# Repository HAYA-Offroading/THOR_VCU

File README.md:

# README for THOR VCU 

## Code related notes 

## PCB Design notes 

### VERSION V1.01 

V1.01 of the PCB was fabricated at Lion Circuits, and used for ESVC 2025.\
Has many errors, and the audio amplifier is not available. Power rails are incorrect, and another buck converter had to be botched into place, and a 5v rail had to be added. <br/>

Images: <br/>

[Front Side of fabricated PCB](https://github.com/HAYA-Offroading/THOR_VCU/blob/main/PCB_V1-01/FrontSide.jpeg)<br/>

[Back Side of fabricated PCB](https://github.com/HAYA-Offroading/THOR_VCU/blob/main/PCB_V1-01/BackSide.jpeg)<br/>

**DO NOT REFABRICATE WITHOUT FIXES.**

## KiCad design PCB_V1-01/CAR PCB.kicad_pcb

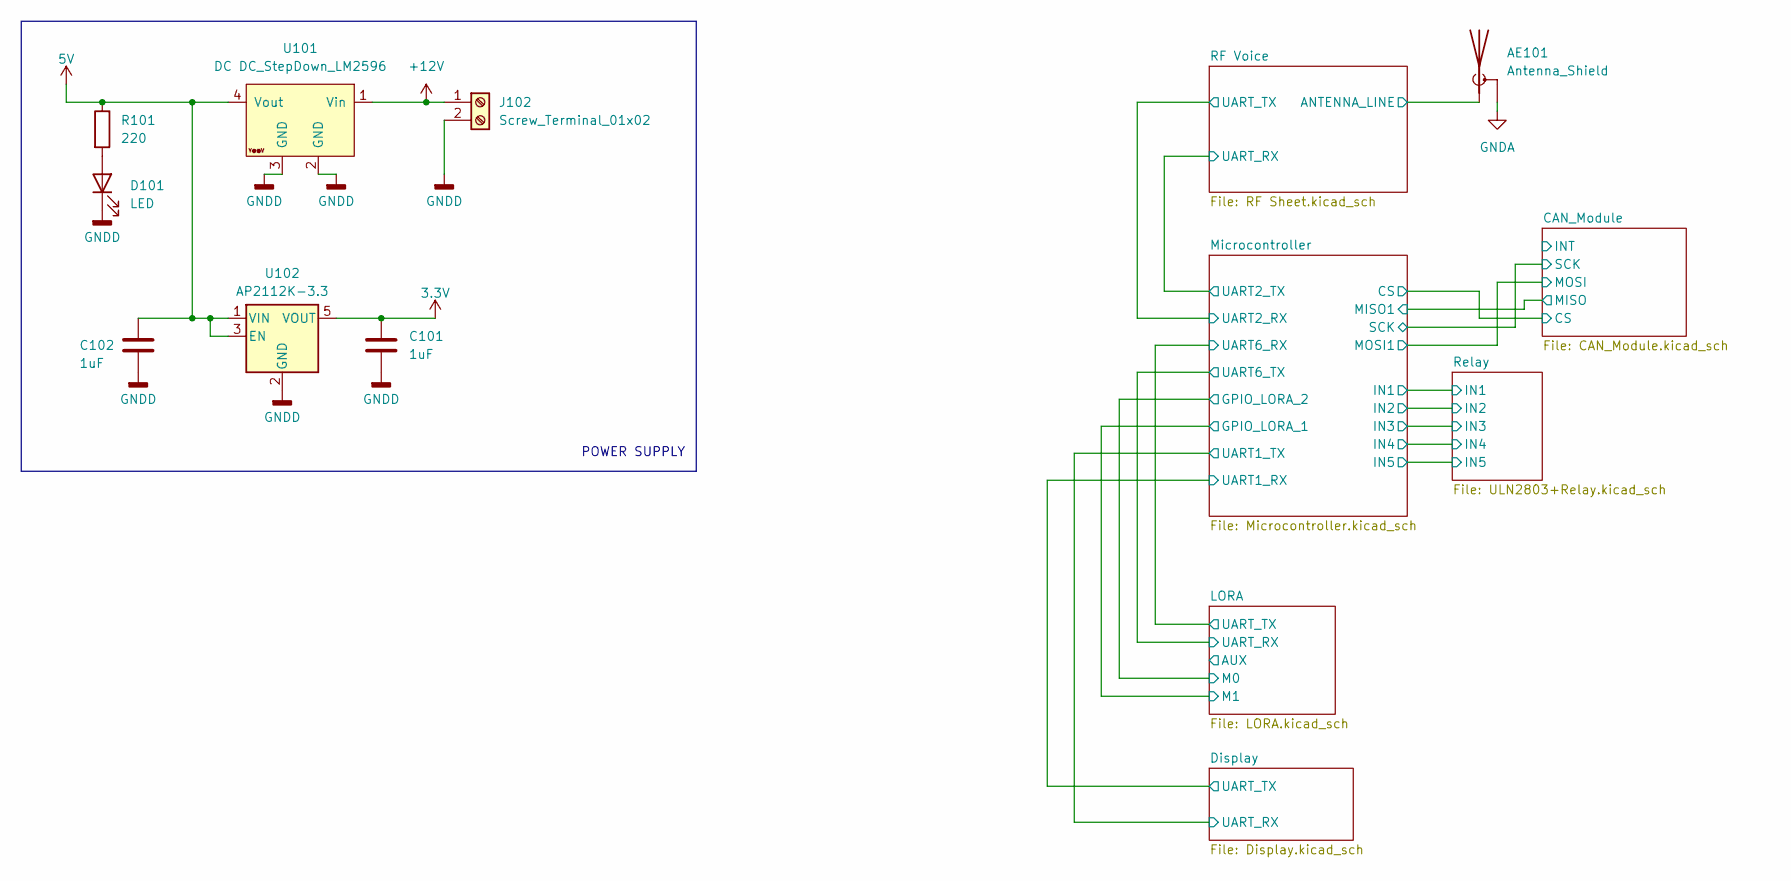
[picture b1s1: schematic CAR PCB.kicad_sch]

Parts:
AE101: Antenna_Shield; SMA_Amphenol_132134-11_Vertical
C101, C102: 1uF; C_0603_1608Metric_Pad1.08x0.95mm_HandSolder
D101: LED; LED_1206_3216Metric_Pad1.42x1.75mm_HandSolder
J102: Screw_Terminal_01x02; TerminalBlock_Phoenix_MKDS-3-2-5.08_1x02_P5.08mm_Horizontal
R101: 220; R_0805_2012Metric_Pad1.20x1.40mm_HandSolder
U101: DC DC_StepDown_LM2596; DCDC_StepDown_LM2596
U102: AP2112K-3.3; SOT-23-5

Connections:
3.3V: C101.1, U102.5 (VOUT); also elsewhere on the board
5V: C102.1, R101.1, U101.4 (Vout), U102.1 (VIN), U102.3 (EN); also elsewhere on the board
+12V: J102.1, U101.1 (Vin); also elsewhere on the board
/RF Voice/ANTENNA_LINE: AE101.1 (A); also elsewhere on the board
GNDA: AE101.2 (Shield); also elsewhere on the board
GNDD: C101.2, C102.2, D101.1 (K), J102.2, U101.2 (GND), U101.3 (GND), U102.2 (GND); also elsewhere on the board
unnamed: D101.2 (A), R101.2

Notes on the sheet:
POWER SUPPLY

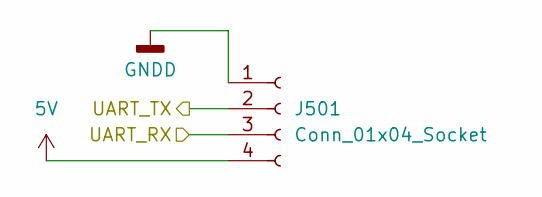
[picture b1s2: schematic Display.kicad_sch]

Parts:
J501: Conn_01x04_Socket; JST_XH_B4B-XH-A_1x04_P2.50mm_Vertical

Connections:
5V: J501.4; also elsewhere on the board
/Display/UART_RX: J501.3; also elsewhere on the board
/Display/UART_TX: J501.2; also elsewhere on the board
GNDD: J501.1; also elsewhere on the board

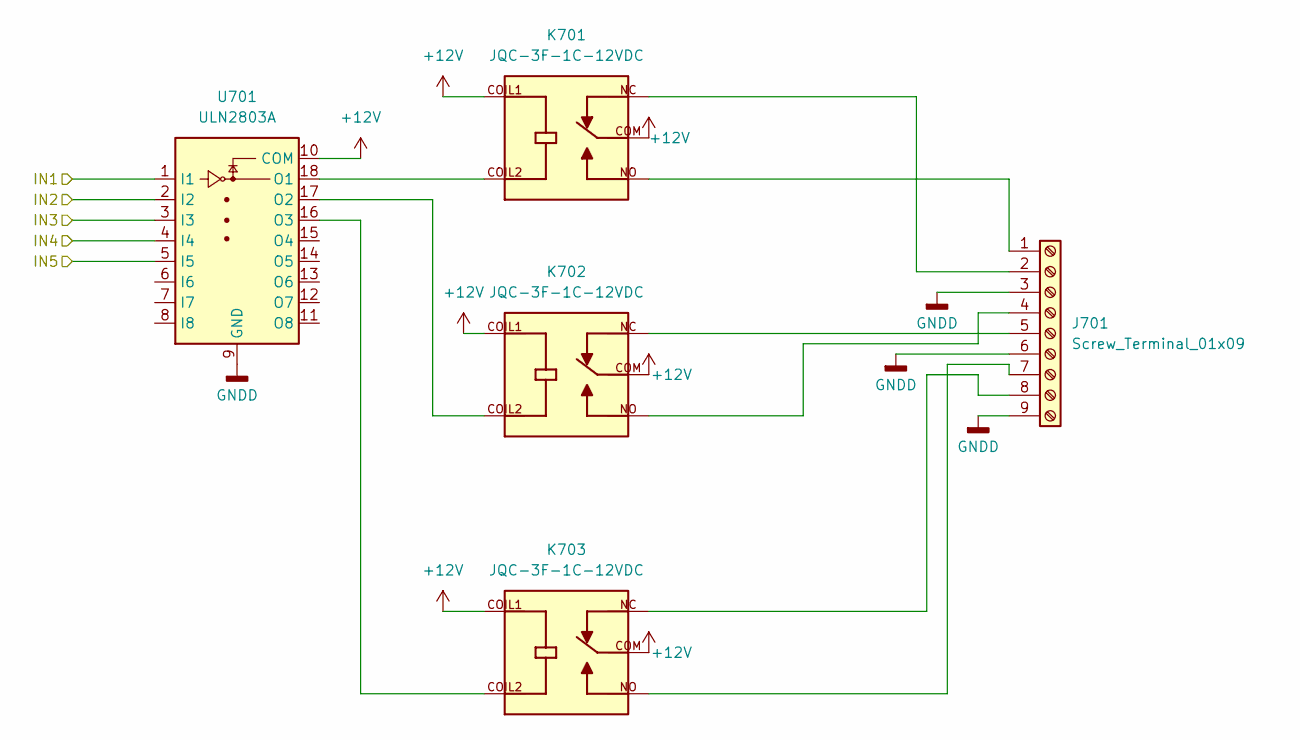
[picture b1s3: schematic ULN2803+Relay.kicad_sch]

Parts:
J701: Screw_Terminal_01x09; TerminalBlock_Phoenix_MKDS-1,5-9_1x09_P5.00mm_Horizontal
K701, K702, K703: JQC-3F-1C-12VDC; RELAY_JQC-3F-1C-24VDC; PARTREV N/A
U701: ULN2803A; SOIC-18W_7.5x11.6mm_P1.27mm

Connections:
+12V: K701.COIL1, K701.COM, K702.COIL1, K702.COM, K703.COIL1, K703.COM, U701.10 (COM); also elsewhere on the board
/Microcontroller/IN1: U701.1 (I1); also elsewhere on the board
/Microcontroller/IN2: U701.2 (I2); also elsewhere on the board
/Microcontroller/IN3: U701.3 (I3); also elsewhere on the board
/Microcontroller/IN4: U701.4 (I4); also elsewhere on the board
/Microcontroller/IN5: U701.5 (I5); also elsewhere on the board
GNDD: J701.3, J701.6, J701.9, U701.9 (GND); also elsewhere on the board
unnamed: J701.1, K701.NO
unnamed: J701.2, K701.NC
unnamed: J701.4, K702.NO
unnamed: J701.5, K702.NC
unnamed: J701.7, K703.NO
unnamed: J701.8, K703.NC
unnamed: K701.COIL2, U701.18 (O1)
unnamed: K702.COIL2, U701.17 (O2)
unnamed: K703.COIL2, U701.16 (O3)

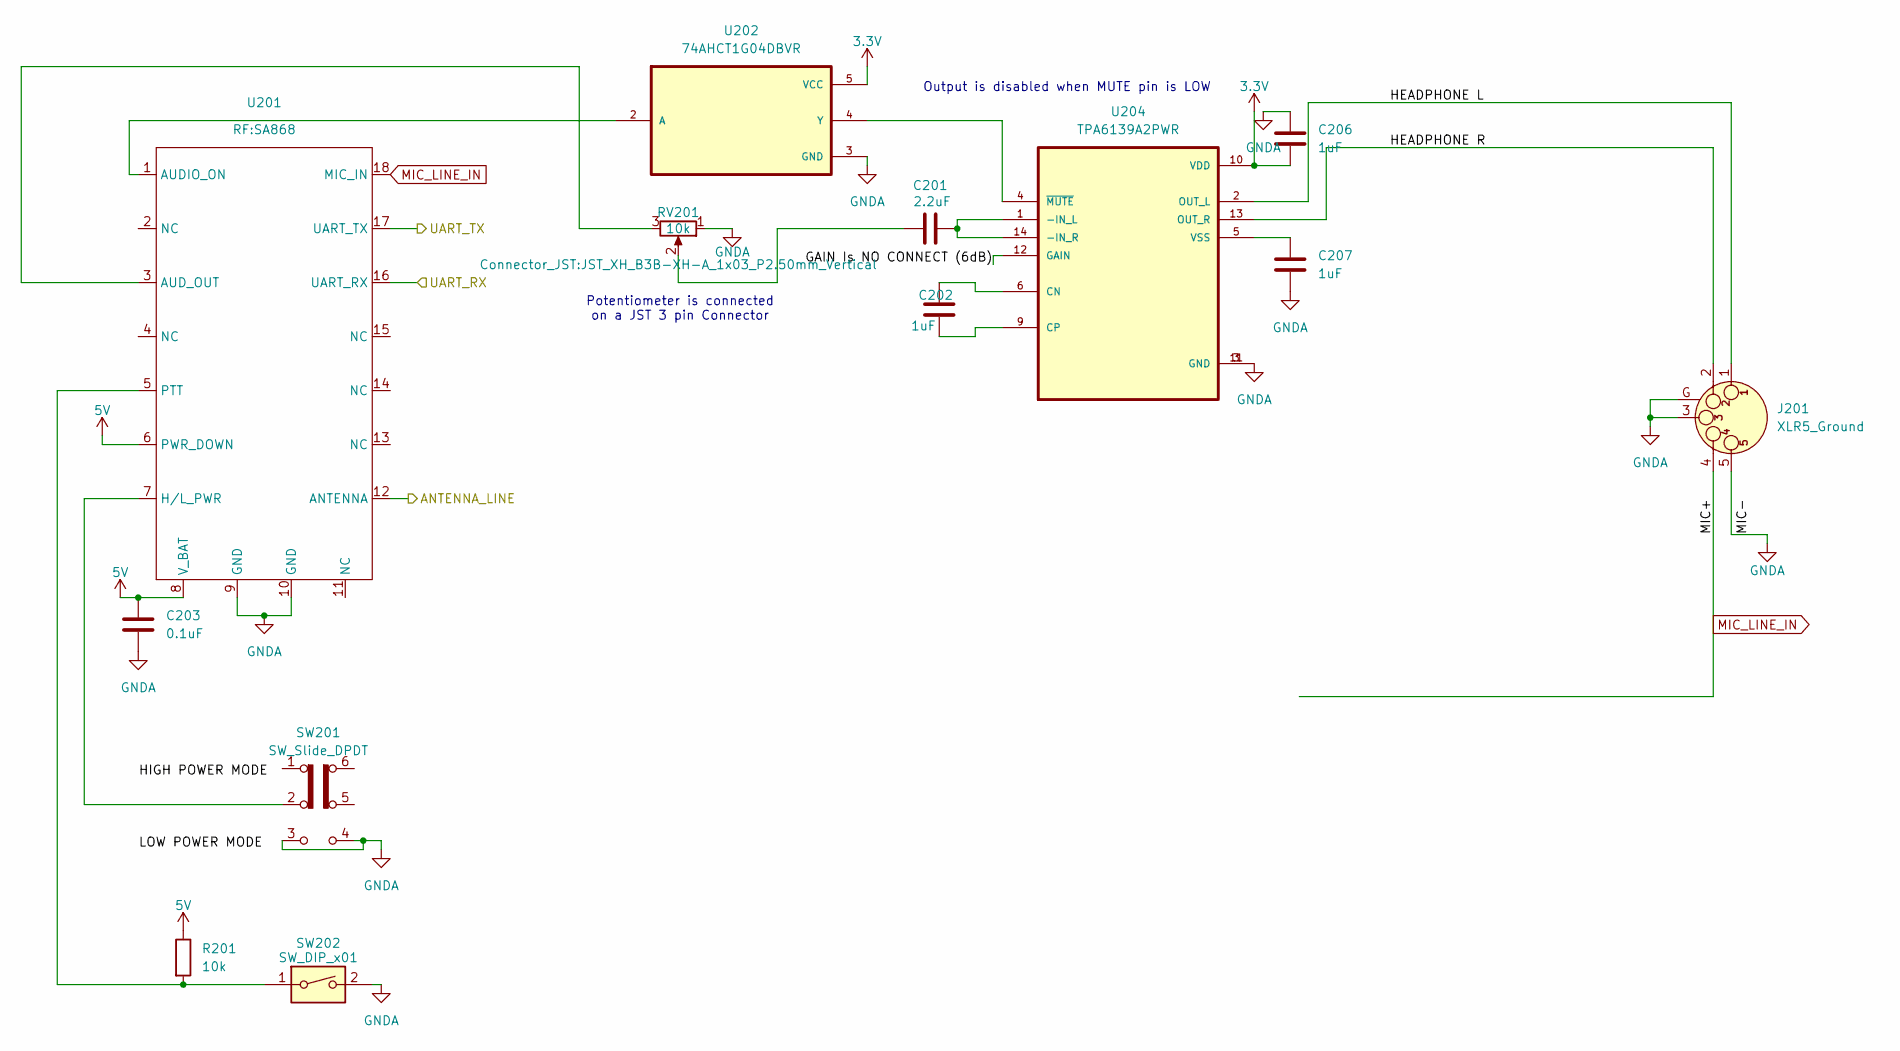
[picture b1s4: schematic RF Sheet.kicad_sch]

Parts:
C201: 2.2uF; C_0603_1608Metric_Pad1.08x0.95mm_HandSolder
C202, C206, C207: 1uF; C_0603_1608Metric_Pad1.08x0.95mm_HandSolder
C203: 0.1uF; C_0603_1608Metric_Pad1.08x0.95mm_HandSolder
J201: XLR5_Ground; JST_XH_B5B-XH-A_1x05_P2.50mm_Vertical
R201: 10k; R_1206_3216Metric_Pad1.30x1.75mm_HandSolder
RV201: 10k; JST_XH_B3B-XH-A_1x03_P2.50mm_Vertical
SW201: SW_Slide_DPDT; JST_XH_B4B-XH-A_1x04_P2.50mm_Vertical
SW202: SW_DIP_x01
U201: SA868
U202: 74AHCT1G04DBVR; SOT-23-5
U204: TPA6139A2PWR; SOP-65P640X120-14N

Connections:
3.3V: C206.2, U202.5 (VCC), U204.10 (VDD); also elsewhere on the board
5V: C203.1, R201.1, U201.6 (PWR_DOWN), U201.8 (V_BAT); also elsewhere on the board
/Microcontroller/UART2_RX: U201.17 (UART_TX); also elsewhere on the board
/Microcontroller/UART2_TX: U201.16 (UART_RX); also elsewhere on the board
/RF Voice/ANTENNA_LINE: U201.12 (ANTENNA); also elsewhere on the board
/RF Voice/GAIN Is NO CONNECT (6dB): U204.12 (GAIN)
/RF Voice/HEADPHONE L: J201.1, U204.2 (OUT_L)
/RF Voice/HEADPHONE R: J201.2, U204.13 (OUT_R)
GNDA: C203.2, C206.1, C207.2, J201.3, J201.5, J201.G, RV201.1, SW201.3 (C), SW201.4 (A), SW202.2, U201.9 (GND), U201.10 (GND), U202.3 (GND), U204.3 (GND), U204.11 (GND); also elsewhere on the board
MIC_LINE_IN: J201.4 (P3), U201.18 (MIC_IN)
unnamed: C201.1, RV201.2
unnamed: U201.1 (AUDIO_ON), U202.2 (A)
unnamed: RV201.3, U201.3 (AUD_OUT)
unnamed: SW201.2 (B), U201.7 (H/L_PWR)
unnamed: R201.2, SW202.1, U201.5 (PTT)
unnamed: U202.4 (Y), U204.4 (~MUTE)
unnamed: C201.2, U204.1 (-IN_L), U204.14 (-IN_R)
unnamed: C202.1, U204.6 (CN)
unnamed: C202.2, U204.9 (CP)
unnamed: C207.1, U204.5 (VSS)

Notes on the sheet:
Potentiometer is connected on a JST 3 pin Connector
Output is disabled when MUTE pin is LOW

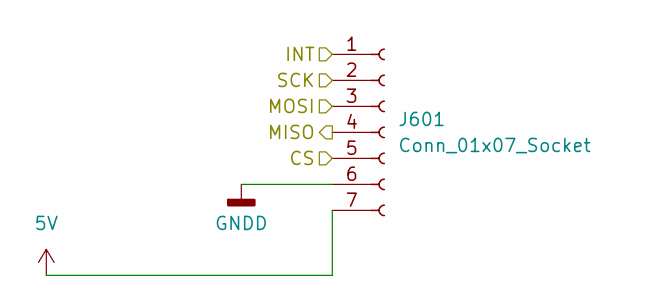
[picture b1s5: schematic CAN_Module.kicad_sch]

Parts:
J601: Conn_01x07_Socket; PinHeader_1x07_P2.54mm_Vertical

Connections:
5V: J601.7; also elsewhere on the board
/CAN_Module/CS: J601.5; also elsewhere on the board
/CAN_Module/INT: J601.1
/CAN_Module/MISO: J601.4; also elsewhere on the board
/CAN_Module/MOSI: J601.3; also elsewhere on the board
/CAN_Module/SCK: J601.2; also elsewhere on the board
GNDD: J601.6; also elsewhere on the board

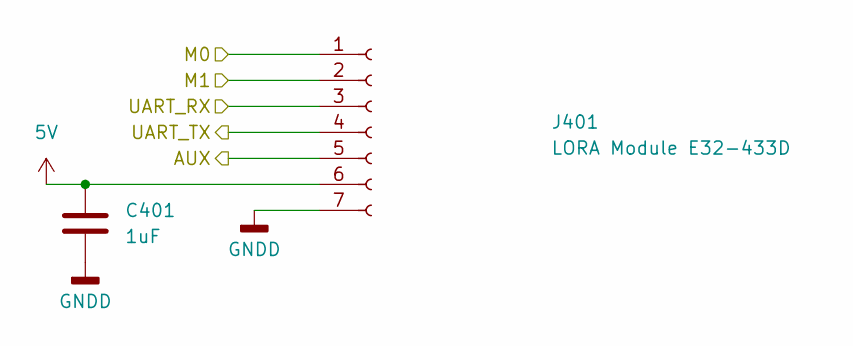
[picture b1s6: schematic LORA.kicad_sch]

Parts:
C401: 1uF; C_0603_1608Metric_Pad1.08x0.95mm_HandSolder
J401: LORA Module E32-433D; E32-433T33D

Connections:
5V: C401.1, J401.6; also elsewhere on the board
/LORA/AUX: J401.5
/LORA/M0: J401.1; also elsewhere on the board
/LORA/M1: J401.2; also elsewhere on the board
/LORA/UART_RX: J401.3; also elsewhere on the board
/LORA/UART_TX: J401.4; also elsewhere on the board
GNDD: C401.2, J401.7; also elsewhere on the board

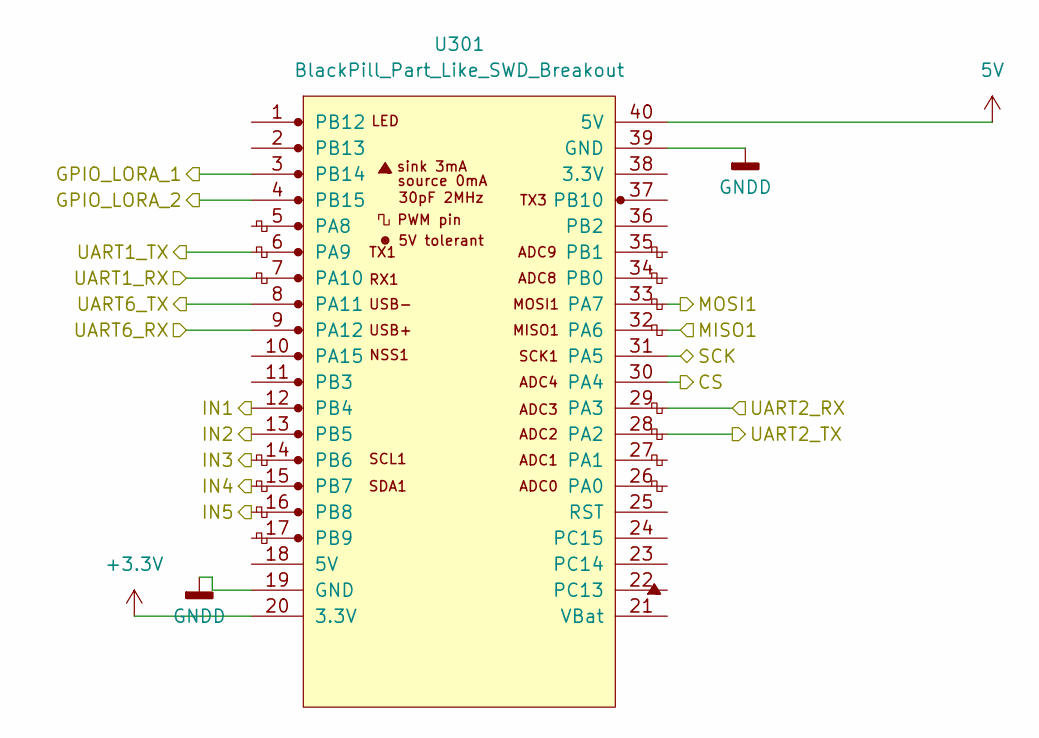
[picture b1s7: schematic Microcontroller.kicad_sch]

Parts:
U301: BlackPill_Part_Like_SWD_Breakout; Blackpill STM32F401CCU6

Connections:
5V: U301.40 (5V); also elsewhere on the board
+3.3V: U301.20 (3.3V)
/CAN_Module/CS: U301.30 (PA4); also elsewhere on the board
/CAN_Module/MISO: U301.32 (PA6); also elsewhere on the board
/CAN_Module/MOSI: U301.33 (PA7); also elsewhere on the board
/CAN_Module/SCK: U301.31 (PA5); also elsewhere on the board
/Display/UART_RX: U301.6 (PA9); also elsewhere on the board
/Display/UART_TX: U301.7 (PA10); also elsewhere on the board
/LORA/M0: U301.4 (PB15); also elsewhere on the board
/LORA/M1: U301.3 (PB14); also elsewhere on the board
/LORA/UART_RX: U301.8 (PA11); also elsewhere on the board
/LORA/UART_TX: U301.9 (PA12); also elsewhere on the board
/Microcontroller/IN1: U301.12 (PB4); also elsewhere on the board
/Microcontroller/IN2: U301.13 (PB5); also elsewhere on the board
/Microcontroller/IN3: U301.14 (PB6); also elsewhere on the board
/Microcontroller/IN4: U301.15 (PB7); also elsewhere on the board
/Microcontroller/IN5: U301.16 (PB8); also elsewhere on the board
/Microcontroller/UART2_RX: U301.29 (PA3); also elsewhere on the board
/Microcontroller/UART2_TX: U301.28 (PA2); also elsewhere on the board
GNDD: U301.19 (GND), U301.39 (GND); also elsewhere on the board

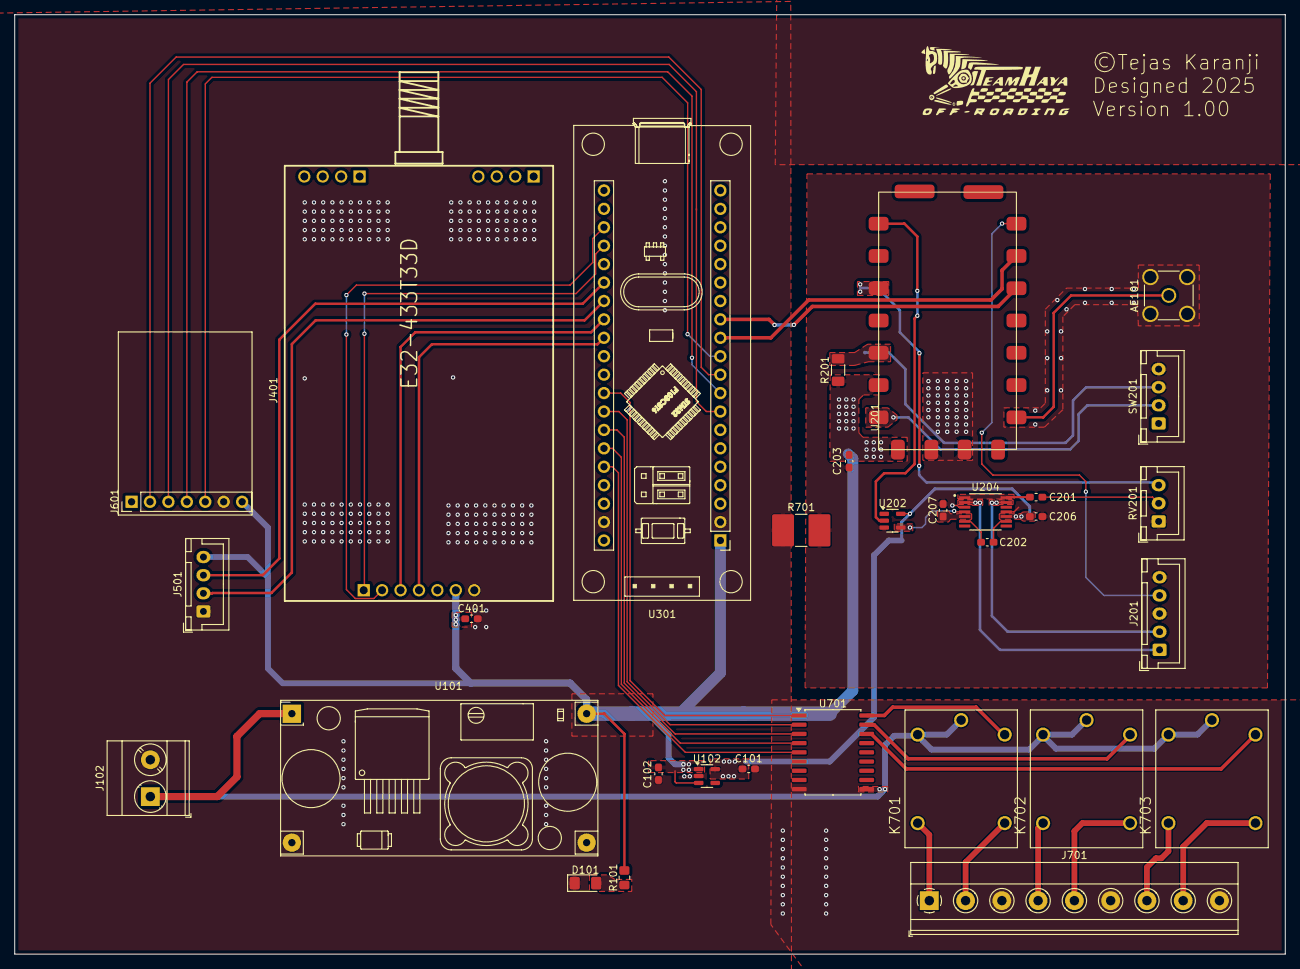
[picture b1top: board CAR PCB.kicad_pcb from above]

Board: 2 copper layers, 175.2 x 129.5 mm, 31 parts (0 on the bottom side), 46 nets.

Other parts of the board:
R701: R_2816_7142Metric

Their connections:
GNDA: R701.2; also elsewhere on the board
GNDD: R701.1; also elsewhere on the board

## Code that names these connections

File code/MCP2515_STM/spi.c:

#include "spi.h"

// SPI Clock = PA5
// SPI MISO = PA6
// SPI MOSI = PA7
// SPI NSS = PA4

void SPI_Init(){
    RCC->AHB1ENR |= RCC_AHB1ENR_GPIOAEN;
    RCC->APB2ENR |= RCC_APB2ENR_SPI1EN;

    GPIOA->MODER |= GPIO_MODER_MODE5_1 | GPIO_MODER_MODE6_1 | GPIO_MODER_MODE7_1 | GPIO_MODER_MODE4_0;
    GPIOA->AFR[0] |= (AFL_AF5 << 20) | (AFL_AF5 << 24) | (AFL_AF5 << 28);

    SPI1->CR1 = 0;
    SPI1->CR1 |= 4 << 3;
    SPI1->CR1 |= SPI_CR1_MSTR;
    SPI1->CR1 |= SPI_CR1_SSM | SPI_CR1_SSI; // Software NSS management
    SPI1->CR1 |= SPI_CR1_SPE;
    SPI_CS_High();
    //Currently CS PIN is LOW
  }

  void SPI_CS_High(){
    while(SPI1->SR & SPI_SR_BSY); // Wait until not busy
    GPIOA->ODR |= GPIO_ODR_OD4;
  }

  void SPI_CS_Low(){
    GPIOA->ODR &= ~(GPIO_ODR_OD4);
  }

  void Start_SPI(){
    SPI1->CR1 |= SPI_CR1_SPE;
    SPI_CS_Low();
  }

  void Stop_SPI(){
    SPI_CS_High();
    SPI1->CR1 &= ~(SPI_CR1_SPE);

  }

  void SPI_Send(uint8_t data){

    while(!(SPI1->SR & SPI_SR_TXE)){};
    SPI1->DR = data;

  }


  void SPI_Send_Buffer (uint8_t *buffer, uint8_t buffer_size){

    for(int i = 0; i < buffer_size; i++){
      while(!(SPI1->SR & SPI_SR_TXE)){};
      SPI1->DR = *(buffer+i);
    }

  }

  int SPI_Receive(){
    int data;

    SPI_Send(0x00);
    while(!(SPI1->SR & SPI_SR_RXNE)){};
    data = SPI1->DR;

    return data;
  }

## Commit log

2025-01-16 initial commit, added display code files
2025-01-16 added dwin files
2025-01-17 added new branch, refined the dgus_tft.c file a little bit
2025-01-19 Create documentation and references folder
2025-01-19 Add DGUS RM
2025-01-21 added tachometer
2025-01-29 added Zephyr codes, used spi apis
2025-02-04 README file modified
2025-02-04 Readme modified
2025-02-04 added images
2025-02-04 readme syntax test
2025-02-04 Revert "README file modified"
    This reverts commit 98836378753e9427077d6bd303dbfc043a2cde8a.
2025-02-04 Modified Readme
2025-02-05 test
2025-02-07 Added CAN Protocol for Kelly Controller
2025-02-07 Added CAN Protocol for Kelly Controller (#4)
2025-06-05 added PCB_V1-01 files and fabrication outputs
2025-06-05 added pcb images
2025-06-05 reorganized folders
2025-06-05 reorganized folders (#9)
2025-06-05 Update README.md (#10)
2025-06-05 Update README.md (#11)
2025-06-05 Update README.md to correct images
2025-06-05 Update README.md to correct images (#12)
2025-06-08 Added MCP2515 lib, has errors in receiving
2025-06-11 added v2.0 initial
2025-06-12 PCB_V2.0_Altium
2025-06-12 Changed relays to mosfets in parallel changed labels to netnames in mcu sheet
2025-06-13 reorganize PCB_V2-0 folder structure
2025-06-15 Schematic errors cleared, folder rearranged, Kicad data removed
2025-06-15 Updated LED Footprints
2025-06-15 Fixed PCF8574 LED Connections
2025-06-15 Added Pheonix terminals footprints from KiCad libs
2025-06-15 added LED library from KiCad
2025-06-16 Changed reference designators - 201 onwards
2025-06-16 Changed reference designators - 301 onwards
2025-06-16 Changed reference designators - 701 onwards
2025-06-16 Changed reference designators - 101 onwards
2025-06-16 Some components placed and routed
2025-06-17 added r705-707 footprints
2025-06-17 Changed reference designators - 201 onwards - Fixed
2025-06-17 Add MCP Altium lib
2025-06-17 Added MCP2515 footprints from altium lib
2025-06-17 Added TJA and MCP footprints
2025-06-17 Add TJA Altium lib
2025-06-17 Added a bunch of shit
2025-06-17 Added SA868 and blackpill footprints
2025-06-17 Routing almost done, PDN remaining
2025-06-17 changed lib file
2025-06-30 Changed MCU from STM32 to ESP32S3-WROOM-1
2025-06-30 Added PAM8403
2025-06-30 Added many libraries
2025-10-25 Routed Antenna, Must perform checks

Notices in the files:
PCB_V1-01/CAR PCB.kicad_pcb:
©Tejas Karanji
